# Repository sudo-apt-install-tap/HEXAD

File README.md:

<div align="center">

<!-- Replace with a logo or a render of the board (width 250 looks good) -->

<h1>
  <b>
    HexAD
  </b>
</h1>

<h3> <b> A 12 pad USB MIDI controller with 6 rotary encoders and a TFT screen! </b> </h3>

</div>

## **Overview**

A USB MIDI controller built around a Raspberry Pi Pico (RP2040) with:

- **12 Cherry MX style pads** in a 4x3 diode matrix, sending MIDI notes
- **6 EC11 rotary encoders with push buttons**, sending MIDI CC messages
- **1.8" 128x160 TFT display** that shows which pads are held, the encoder levels and the last MIDI message
- **MCP23017 I2C expander** that reads the encoder A/B lines, because the Pico ran out of GPIOs
- Class compliant **USB MIDI**, so there are no drivers to install
- No Case required, absolutely no 3d print needed!

### Why?

I wanted a proper MIDI controller with real pads, real knobs and a screen that tells me what is going on, instead of guessing which knob does what. It also gave me a reason to design a board with a GPIO expander for the first time.

also because KNOBS.

### How?

The firmware is in [firmware](firmware). It is written with the Arduino-Pico core and TinyUSB MIDI. Core 0 scans the pads, the encoders and sends the MIDI. Core 1 only draws the display, so a screen refresh never makes the knobs lag.

The pads are plain switches, so they send a fixed velocity of 100.

#### MIDI map

| Control | Message | Notes |
| --- | --- | --- |
| Pads (bottom row, left to right) | Note 36 to 39 | Channel 1 |
| Pads (middle row) | Note 40 to 43 | Channel 1 |
| Pads (top row) | Note 44 to 47 | Channel 1 |
| Encoders 1 to 6 | CC 20 to 25 | Absolute value, starts at 64, steps of 2 |
| Encoder buttons 1 to 6 | CC 30 to 35 | 127 when pressed, 0 when released |

#### Pin map

| Function | Pins |
| --- | --- |
| Pad matrix columns | GPIO0 to GPIO3 |
| Pad matrix rows | GPIO4 to GPIO6 |
| Encoder buttons | GPIO7, 10, 11, 12, 16, 17 |
| I2C (MCP23017 at 0x27) | SDA GPIO8, SCL GPIO9 |
| TFT (SPI0) | SCK GPIO18, MOSI GPIO19, CS GPIO14, DC GPIO13, RST GPIO15 |

The MCP23017 runs on 3.3V with 4.7k pull-ups on SDA and SCL. Its address pins are pulled high with solder jumpers to ground, so you can change the I2C address without touching the firmware wiring. The spare GPB4 to GPB7 pins are broken out on a 4 pin header.

## CAD
CAD files are available at [/CAD](/CAD).

## Images
<div align="center">

<br> Full render<br>

---

<br> PCB

---

<br> Sch

---

<br> 3D Viewer

---

</div>

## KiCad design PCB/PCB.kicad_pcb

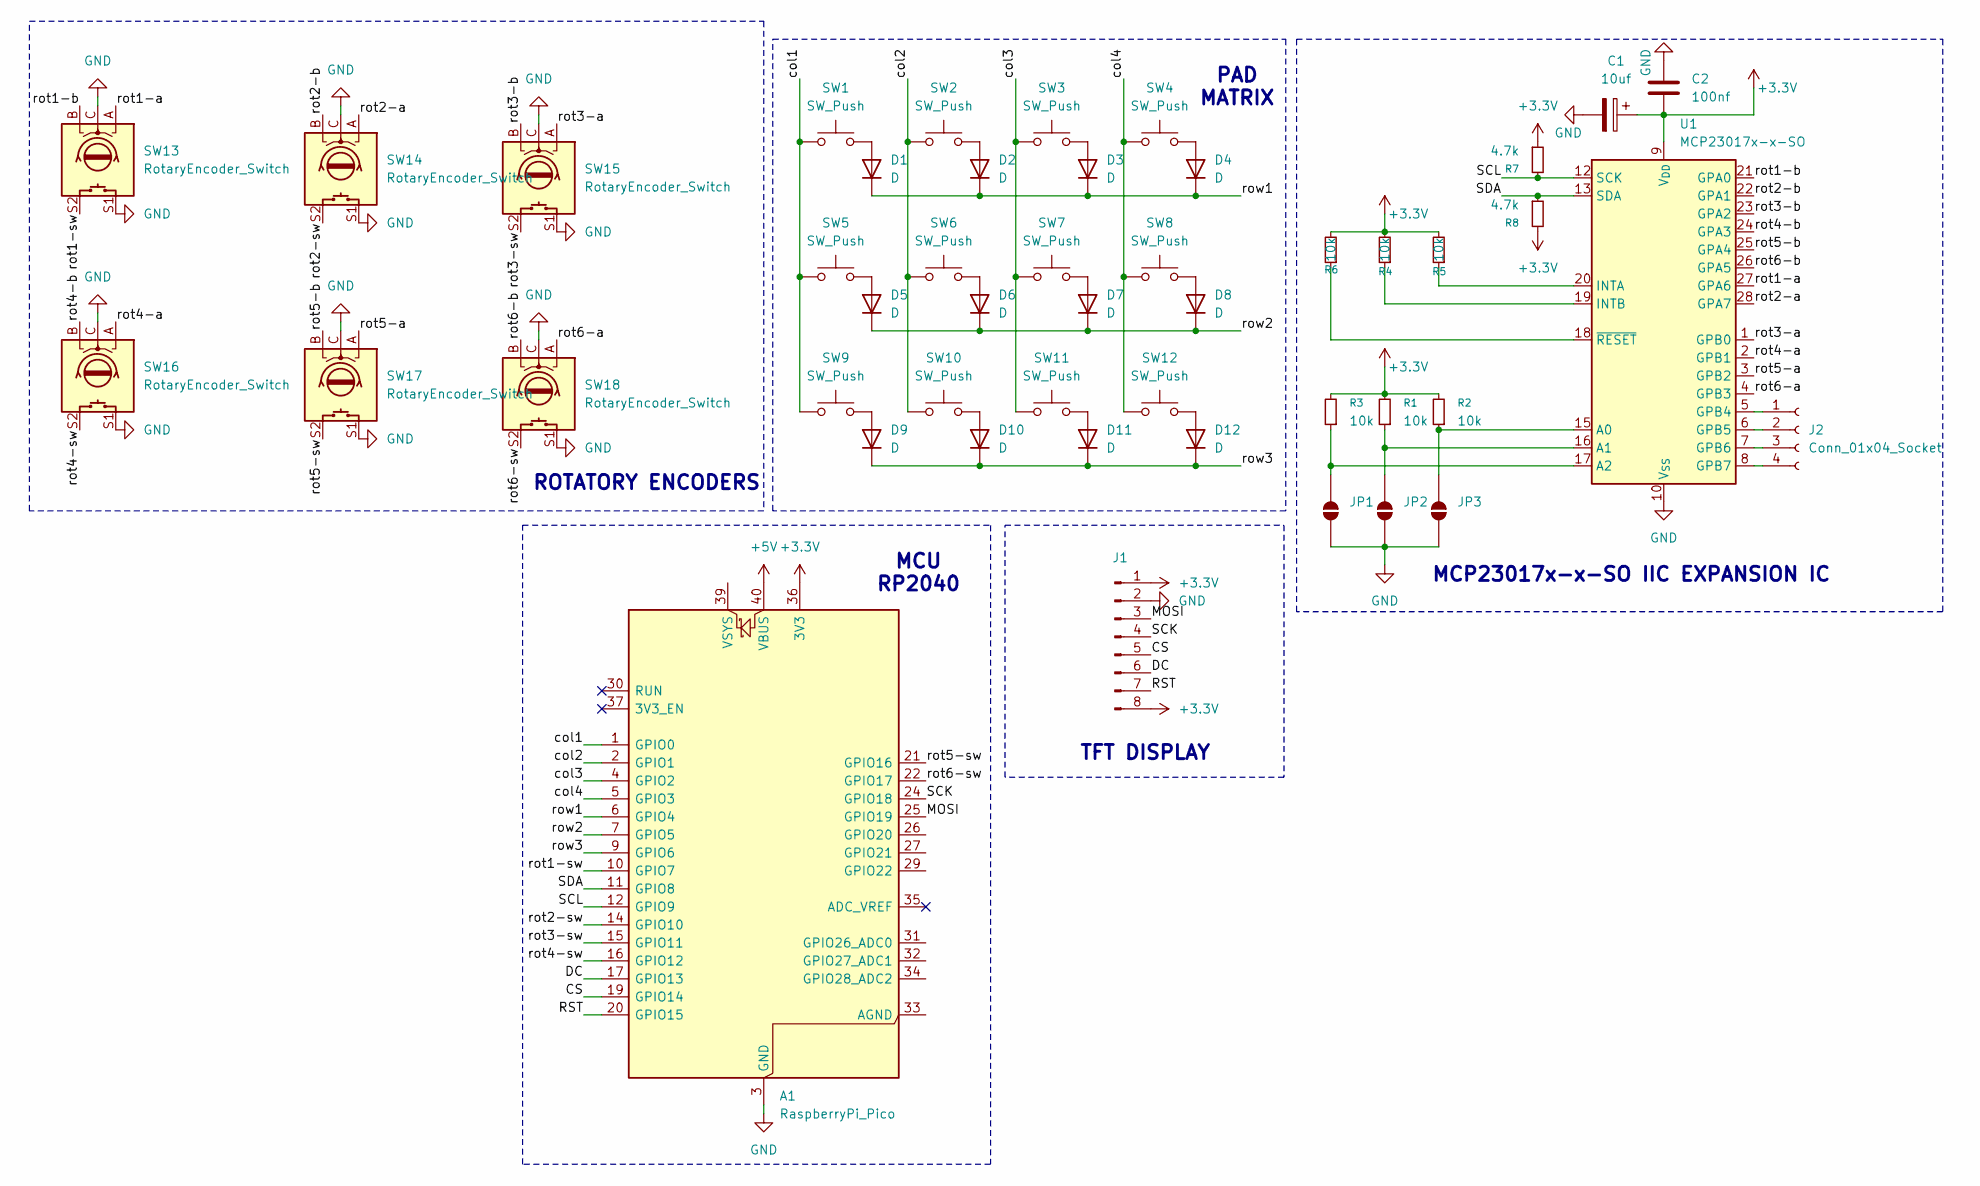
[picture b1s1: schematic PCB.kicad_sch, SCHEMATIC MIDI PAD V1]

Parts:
A1: RaspberryPi_Pico; RaspberryPi_Pico_Common_Unspecified
C1: 10uf; CP_Radial_D5.0mm_P2.00mm
C2: 100nf; C_Disc_D5.0mm_W2.5mm_P5.00mm
D1, D2, D3, D4, D5, D6, D7, D8, D9, D10, D11, D12: D; D_DO-35_SOD27_P7.62mm_Horizontal
J1: Conn_01x08_Pin; 1_8INCH_LCD_MODULE
J2: Conn_01x04_Socket; PinHeader_1x04_P2.54mm_Vertical
JP1, JP2, JP3: SolderJumper_2_Open; SolderJumper-2_P1.3mm_Open_RoundedPad1.0x1.5mm
R1, R2, R3, R4, R5, R6: 10k; R_Axial_DIN0204_L3.6mm_D1.6mm_P5.08mm_Horizontal
R7, R8: 4.7k; R_Axial_DIN0204_L3.6mm_D1.6mm_P5.08mm_Horizontal
SW1, SW2, SW3, SW4, SW5, SW6, SW7, SW8, SW9, SW10, SW11, SW12: SW_Push; SW_Cherry_MX_PCB_1.00u
SW13, SW14, SW15, SW16, SW17, SW18: RotaryEncoder_Switch; RotaryEncoder_Alps_EC11E-Switch_Vertical_H20mm_CircularMoun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
U1: MCP23017x-x-SO; SOIC-28W_7.5x17.9mm_P1.27mm

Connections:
+3.3V: A1.36 (3V3), C1.1, C2.2, J1.1, J1.8, R1.2, R2.2, R3.2, R4.2, R5.2, R6.2, R7.1, R8.2, U1.9 (V_{DD})
+5V: A1.40 (VBUS)
/CS: A1.19 (GPIO14), J1.5
/DC: A1.17 (GPIO13), J1.6
/MOSI: A1.25 (GPIO19), J1.3
/RST: A1.20 (GPIO15), J1.7
/SCK: A1.24 (GPIO18), J1.4
/SCL: A1.12 (GPIO9), R7.2, U1.12 (SCK)
/SDA: A1.11 (GPIO8), R8.1, U1.13 (SDA)
/col1: A1.1 (GPIO0), SW1.1, SW5.1, SW9.1
/col2: A1.2 (GPIO1), SW2.1, SW6.1, SW10.1
/col3: A1.4 (GPIO2), SW3.1, SW7.1, SW11.1
/col4: A1.5 (GPIO3), SW4.1, SW8.1, SW12.1
/rot1-a: SW13.A, U1.27 (GPA6)
/rot1-b: SW13.B, U1.21 (GPA0)
/rot1-sw: A1.10 (GPIO7), SW13.S2
/rot2-a: SW14.A, U1.28 (GPA7)
/rot2-b: SW14.B, U1.22 (GPA1)
/rot2-sw: A1.14 (GPIO10), SW14.S2
/rot3-a: SW15.A, U1.1 (GPB0)
/rot3-b: SW15.B, U1.23 (GPA2)
/rot3-sw: A1.15 (GPIO11), SW15.S2
/rot4-a: SW16.A, U1.2 (GPB1)
/rot4-b: SW16.B, U1.24 (GPA3)
/rot4-sw: A1.16 (GPIO12), SW16.S2
/rot5-a: SW17.A, U1.3 (GPB2)
/rot5-b: SW17.B, U1.25 (GPA4)
/rot5-sw: A1.21 (GPIO16), SW17.S2
/rot6-a: SW18.A, U1.4 (GPB3)
/rot6-b: SW18.B, U1.26 (GPA5)
/rot6-sw: A1.22 (GPIO17), SW18.S2
/row1: A1.6 (GPIO4), D1.1 (K), D2.1 (K), D3.1 (K), D4.1 (K)
/row2: A1.7 (GPIO5), D5.1 (K), D6.1 (K), D7.1 (K), D8.1 (K)
/row3: A1.9 (GPIO6), D9.1 (K), D10.1 (K), D11.1 (K), D12.1 (K)
GND: A1.3 (GND), A1.8 (GND), A1.13 (GND), A1.18 (GND), A1.23 (GND), A1.28 (GND), A1.38 (GND), C1.2, C2.1, J1.2, JP1.1 (A), JP2.1 (A), JP3.1 (A), SW13.C, SW13.S1, SW14.C, SW14.S1, SW15.C, SW15.S1, SW16.C, SW16.S1, SW17.C, SW17.S1, SW18.C, SW18.S1, U1.10 (V_{SS})
unnamed: D1.2 (A), SW1.2
unnamed: D2.2 (A), SW2.2
unnamed: D3.2 (A), SW3.2
unnamed: D4.2 (A), SW4.2
unnamed: D5.2 (A), SW5.2
unnamed: D6.2 (A), SW6.2
unnamed: D7.2 (A), SW7.2
unnamed: D8.2 (A), SW8.2
unnamed: D9.2 (A), SW9.2
unnamed: D10.2 (A), SW10.2
unnamed: D11.2 (A), SW11.2
unnamed: D12.2 (A), SW12.2
unnamed: J2.1, U1.5 (GPB4)
unnamed: J2.2, U1.6 (GPB5)
unnamed: J2.3, U1.7 (GPB6)
unnamed: J2.4, U1.8 (GPB7)
unnamed: JP1.2 (B), R3.1, U1.17 (A2)
unnamed: JP2.2 (B), R1.1, U1.16 (A1)
unnamed: JP3.2 (B), R2.1, U1.15 (A0)
unnamed: R5.1, U1.20 (INTA)
unnamed: R4.1, U1.19 (INTB)
unnamed: R6.1, U1.18 (~RESET)

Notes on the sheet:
MCU RP2040
ROTATORY ENCODERS
PAD MATRIX
TFT DISPLAY
MCP23017x-x-SO IIC EXPANSION IC

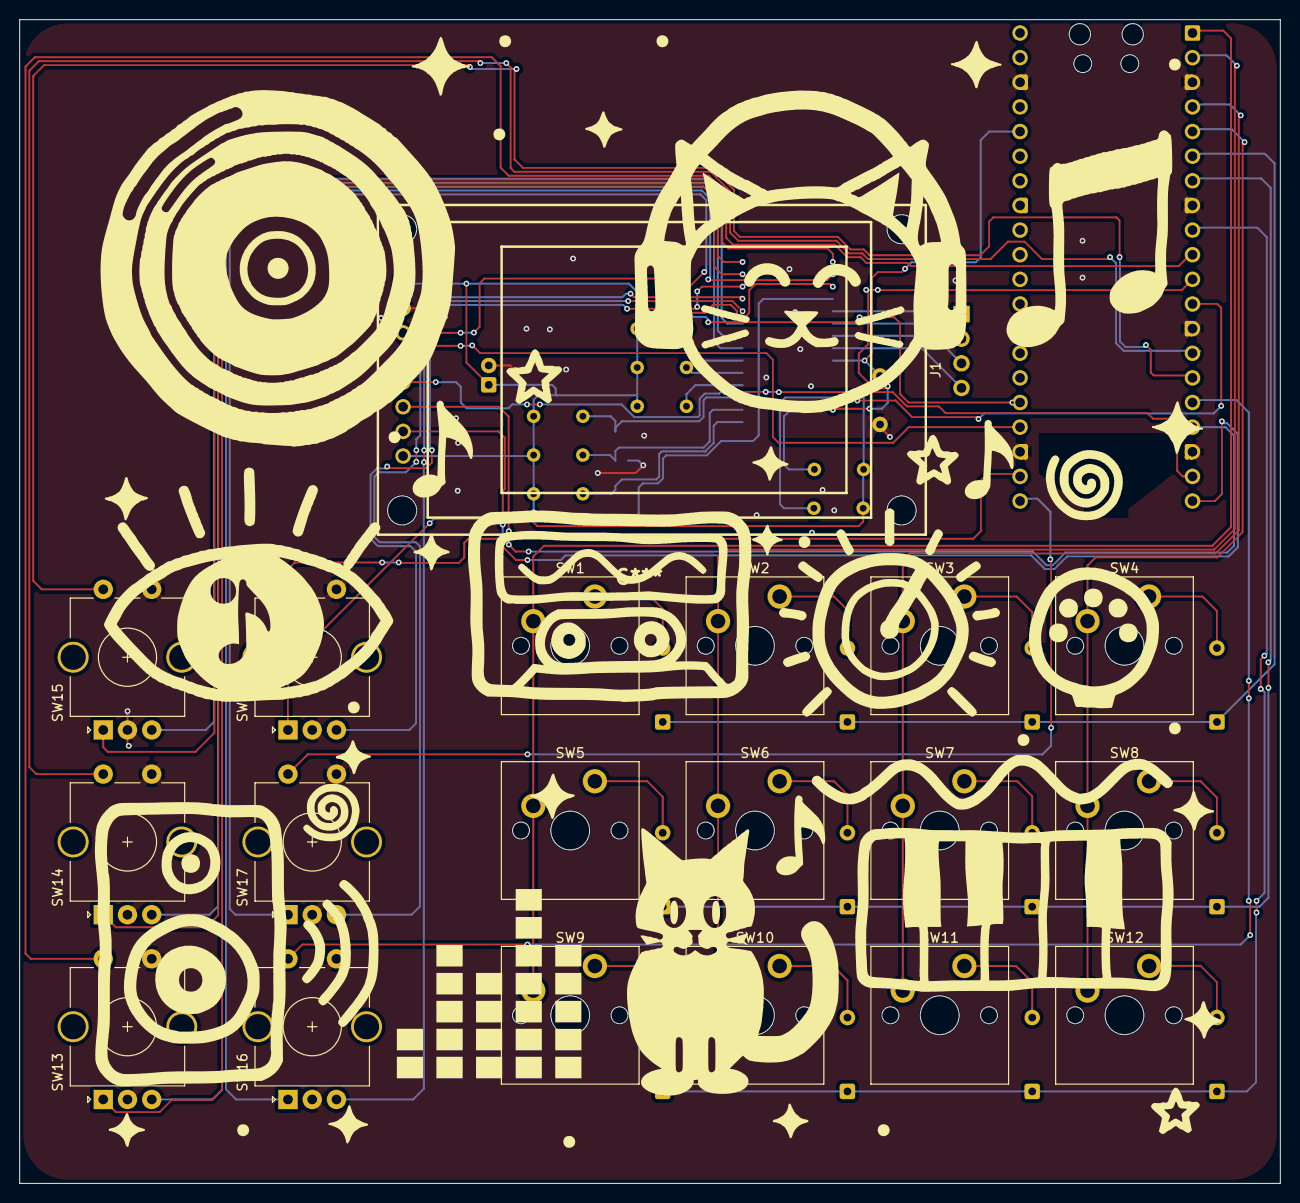
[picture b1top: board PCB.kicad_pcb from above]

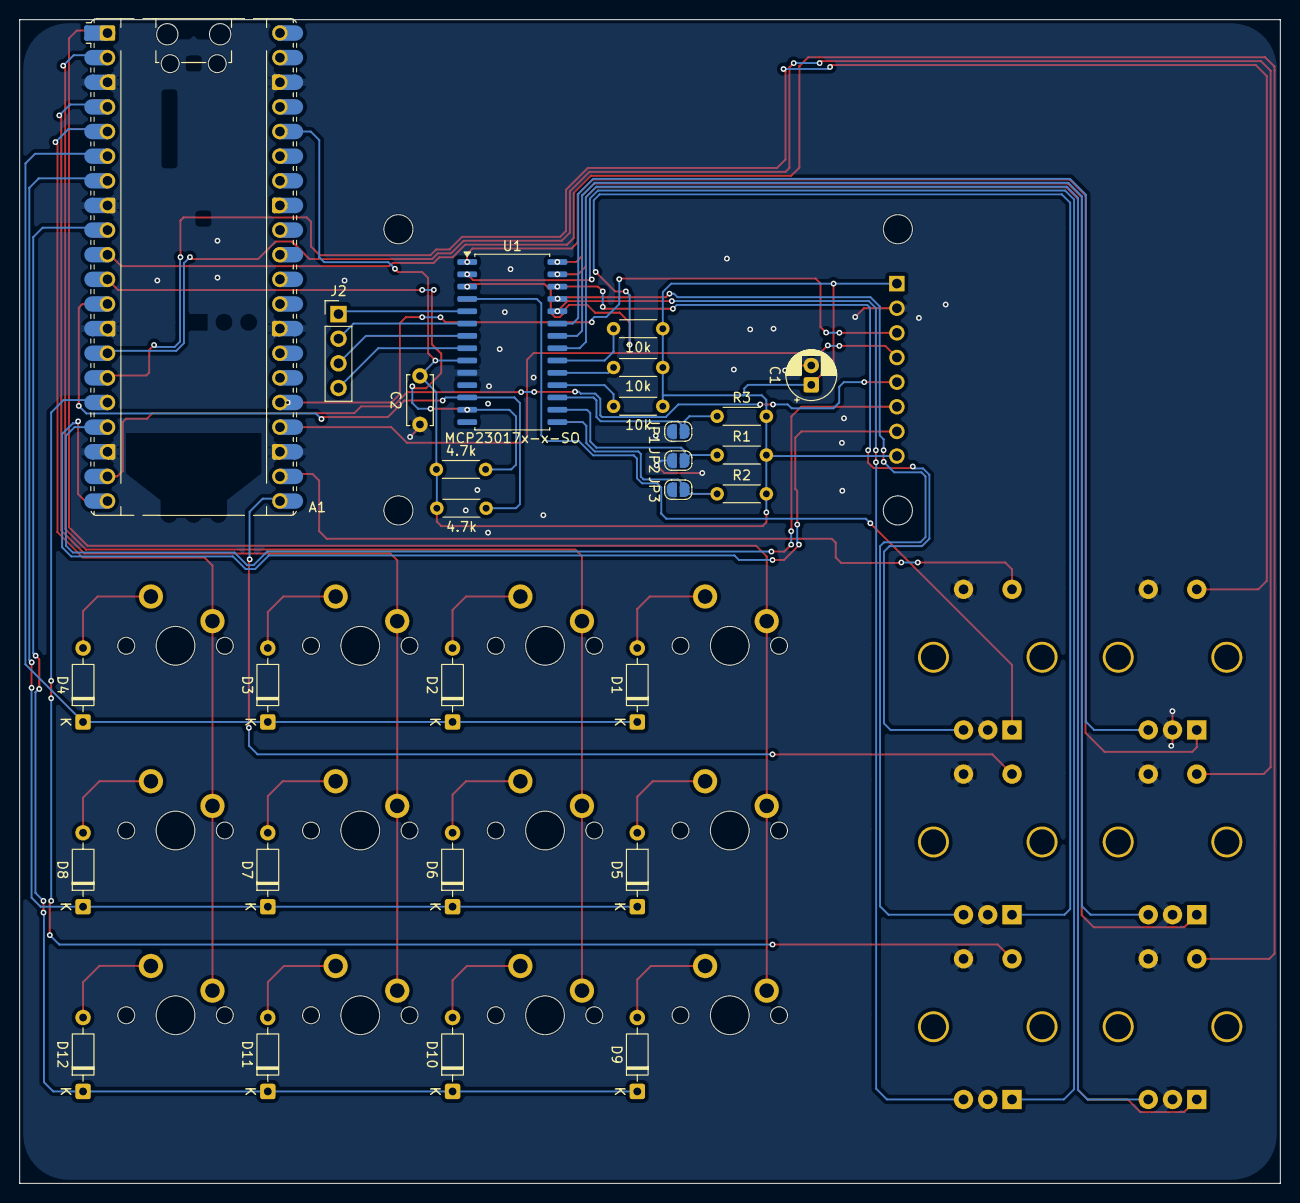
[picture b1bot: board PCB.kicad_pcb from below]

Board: 2 copper layers, 130.0 x 120.0 mm, 47 parts (28 on the bottom side), 56 nets.
